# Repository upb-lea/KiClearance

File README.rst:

.. sectnum::

Welcome to KiClearance
==================================================

This Python program converts a given table of voltage distances into KiCad design rules.

.. image:: docs/source/figures/overview.png

Installation
---------------------------------------
Install KiClearance directly from pyPI:

::

    pip install kiclearance

Usage
---------------------------------------

Define net classes in your KiCad project
~~~~~~~~~~~~~~~~~~~~~~~~~~~~~~~~~~~~~~~~
Add the net classes to each connection in the circuit diagram.

.. image:: docs/source/figures/net_class_directive_labels.png

Add the same net classes in the net classes of the PCB editor:
``KiCad PCB Editor``: ``File`` -> ``Board Setup`` -> ``Design Rules`` -> ``Net classes``

.. image:: docs/source/figures/board_setup.png

Run KiClearance to initially generate the clearance table
~~~~~~~~~~~~~~~~~~~~~~~~~~~~~~~~~~~~~~~~~~~~~~~~~~~~~~~~~

Navigate to the project folder with the KiCad project. Open a terminal and execute :

::

    python -m kiclearance

Now a file ``clearance.ods`` is generated, which contains the human-readable clearance table.
As of now, the table has been generated using fantasy values.

Adapt the table 'clearance.ods/xls/csv' containing clearance distances
~~~~~~~~~~~~~~~~~~~~~~~~~~~~~~~~~~~~~~~~~~~~~~~~~~~~~~~~~~~~~~~~~~~~~~

Update the table (clearance.ods/xls/csv) in your KiCad project directory with voltage clearances defined by your requirements (e.g. standards).

The table contains the distances from a potential to another in ``mm``. The same net distance is optional.

.. image:: docs/source/figures/table.png

Run KiClearance again, to generate the final set of rules for KiCad
~~~~~~~~~~~~~~~~~~~~~~~~~~~~~~~~~~~~~~~~~~~~~~~~~~~~~~~~~~~~~~~~~~~

Navigate to the project folder with the KiCad project and the clearance.ods/.xls/.csv file. Open a terminal and execute :

::

    python -m kiclearance

Now a file ``yourprojectname.kicad_dru`` is generated, which contains the rule sets.

Open your KiCad project, the rule sets are now stored and you can start the routing.

As the inner layers are exposed to less dirt and no air, the distance in the inner layers can be set as optional with a scaling factor (defaults to 1).
If this factor is to be set differently, this can be set with the following command (in the example: inner distance to 75% of outer distance):

::

    python -m kiclearance -i 0.75

To see help and options, run

::

    python -m kiclearance --help

::

    The following arguments are possible:
    -h, --help: Prints this information,
    -f, --project_folder (Optional): Path to the folder in which the project is located. Default: Folder in which this python script is located.
    -n, --project_name (Optional): Name of the kicad project (file prefix). Default: Script will look for a file with .kicad_pro in the set folder.
    -t, --table_file (Optional): Name (and ending) of the file containing the distance values. Default name: 'clearance'.
    -i, --factor_inner_layers (Optional): Reduced factor for the inner layers. Default: 1.0
    -d, --min_track_distance (Optional): minimum track distance between two tracks on the same potential. Default: 0.15 mm.

Tips and tricks
---------------------------------------
Requires KiCad 9 or higher.

If two network classes are assigned to a connection by mistake, `KiClearance` raises an error.

KiCad works through the rules from bottom to top:  Once an applicable rule has been found, KiCad will not search for further rules. Keep this in mind when adding more own rules except from this script here.

Connections in the circuit diagram without a NetClass are automatically assigned to the ``default`` NetClass. 
To avoid careless errors due to missing NetClasses, the ``default`` NetClass should not be used and the distance from ``default`` to other NetClasses should also be set to an unrealistically high value (e.g. 100mm). 
This means that missing NetClasses are immediately noticeable in the layout and can then be assigned.

Example
---------------------------------------
A complete example can be found `here <https://github.com/upb-lea/KiClearance/tree/main/examples>`__.

Documentation
---------------------------------------

Find the documentation `here <https://upb-lea.github.io/KiClearance/index.html>`__.

Troubleshooting
---------------------------------------
* This program has so far been tested only on Linux and Windows.
* For performance reasons when routing, the number of NetClasses should be less than 10 (or not exceed this to any significant degree)
* Using another factor for the inner layers than 1 increases the number of rules and routing might be slower

Known Issue: Old, non existing Nets raise an error
---------------------------------------------------
KiClearance raises an error, here for the exemplary no longer existing net ``ExampleNet``, which has two nets classes assigned ``GND1`` and ``GND2``:    

::

    'ExampleNet' has multiple net classes assigned: ['GND1', 'GND2']

As the ``ExampleNet`` no longer exists in the schematic, it seems like it is an not deleted orphan in the ``.kicad_pro`` file. To resolve this, open the project ``.kicad_pro`` file with an editor and delete these lines (needs adaption for your net names and net classes):

::

    "ExampleNet": [
      "GND1",
      "GND2",
    ],
    
Save the file, and run ``KiClearance`` again.

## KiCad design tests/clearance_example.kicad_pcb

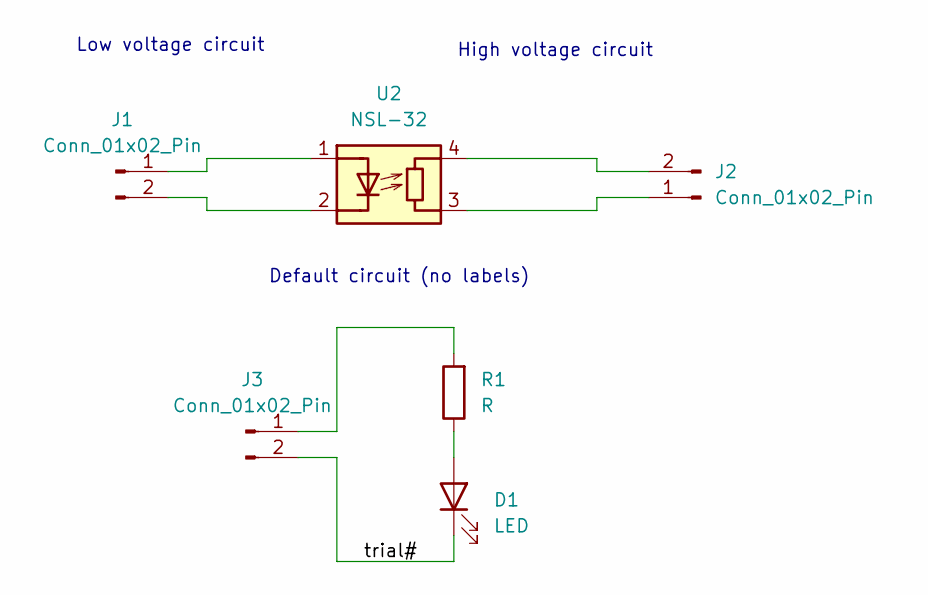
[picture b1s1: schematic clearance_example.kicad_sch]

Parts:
D1: LED; LED_0603_1608Metric
J1, J2, J3: Conn_01x02_Pin; PinHeader_1x02_P1.27mm_Horizontal
R1: R; R_0603_1608Metric
U2: NSL-32; Luna_NSL-32

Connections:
unnamed: D1.2 (A), R1.1
unnamed: D1.1 (K), J3.2
unnamed: J1.1, U2.1 (A)
unnamed: J1.2, U2.2 (K)
unnamed: J2.1, U2.3 (R)
unnamed: J2.2, U2.4 (R)
unnamed: J3.1, R1.2

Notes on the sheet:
Default circuit (no labels)
High voltage circuit
Low voltage circuit

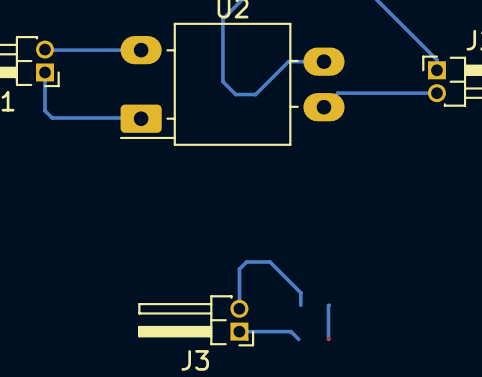
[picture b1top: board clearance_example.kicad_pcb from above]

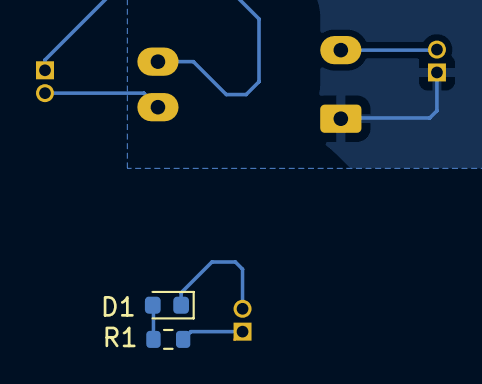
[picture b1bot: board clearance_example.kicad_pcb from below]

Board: 2 copper layers, 6 parts (2 on the bottom side), 7 nets.

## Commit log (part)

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2024-05-18 sphinx documentation setup
2024-05-19 update documentation
2024-05-19 rename project
2024-05-19 add workflows for docu and linting
2024-05-19 deploy: fccdf992384a36144959293ec39d6a9a8772a9da
2024-05-19 make skript executable from terminal by __main__.py
2024-05-19 deploy: 1e1d516a291b4e80304d130382f07359a2da6f41
2024-05-19 ruff linting
2024-05-19 add changelog
2024-05-19 deploy: 03d0492a6f39b173390345dc91629f2ade472717
2024-05-19 fix docu link
2024-05-19 bump version to 0.0.2
2024-05-19 deploy: b7f799b7100d5a92044aefe60e9f8dbe3497c704
2024-05-19 fix old package name
2024-05-19 deploy: 16a0c8b49c72afeec292eb38e5cda23baaf9325f
2024-05-21 add tips and tricks section
2024-05-21 deploy: c95f459937178626b81f1022ac3af619123f6b70
2024-05-22 add hints to rule working
2024-05-22 deploy: f3493cf95cb90d75b08855ad43f15dcacdb50e2a
2024-06-06 add openpyxl as dependency to open xlsx files
2024-06-14 docu update, add dependency to read xlsx
2024-06-14 deploy: f228a82ad694f2b2966789292a3e6af69e5ee884
2024-06-14 fix command line output, bump version to 0.1.1
2024-06-14 deploy: 097f918e267bb5e753a772df8a81becc94e7fbcd
2024-06-14 title underline
2024-06-14 fix issues when -i and -d parameters are missing in terminal usage
2024-06-14 bump version to 0.1.2
2024-06-14 deploy: e2f7711f7039b6cee0749f409e33022d534039ac
2024-08-15 add docstring parameter checker
2024-08-15 deploy: 0d78121b209ccb76144d7e7fc1b8460ad995b340
2025-02-17 add hint to avoid mistakes by the default netclass
2025-02-17 deploy: 739cc9a217a8e07085a73821b0eca149de10121a
2025-05-14 enable mypy in ci
2025-05-14 deploy: 52eeca5a996842e72d961d8e4489976f7318d6e2
2025-05-14 enable pyspelling in ci
2025-05-14 enable pyspelling for readme and changelog
2025-05-14 add integration tests
2025-05-14 fix future warning
2025-05-14 fix linting
2025-05-14 fix pytest
2025-05-14 add codecheck script
2025-05-14 pyspelling read comments
2025-09-03 reduce ruleset in case of factor_inner_layers is 1.0
2025-09-03 deploy: 2cc697b41c649e2848fc41151a321a35cd9aa1ee
2025-09-03 fix pyspelling
2025-09-03 update pytests
2025-09-04 Introduce clearance table generation and clearance automatic table update from kicad project
2025-09-04 deploy: f1ea5fa9b1ea76b155ec628b01e5c949f30a546a
2025-09-04 fix mypy issue
2025-09-05 update readme usage due to automatic table generation
2025-09-05 deploy: c9c393c161c720663ae0a533c9c1855007281034
2025-09-05 simplify initial clearance table generation
2025-09-05 add pyyaml as requirement
2025-09-05 bump version to 0.2.0
2025-09-05 deploy: 4ae0ddcdc88e530a28d98bd50ad8d9b24f0be22a
2025-10-01 raise error in case of multiple net classes are assigned to a single net
2025-10-01 update test kicad files to kicad 9 files
2025-10-01 update readme for requires KiCad 9 or higher, error in case of multiple net classes assigned to a single net
2025-10-01 bump version to 0.2.1
